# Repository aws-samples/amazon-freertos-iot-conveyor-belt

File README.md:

## IoT Conveyor Belt

A 3D Printed Conveyor belt that runs Amazon FreeRTOS to control conveyor direction and report conveyor telemetry data using Amazon's IoT service.

## License

This library is licensed under the Apache 2.0 License.

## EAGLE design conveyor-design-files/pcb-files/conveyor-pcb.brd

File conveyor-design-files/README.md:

# Assembly Instructions Coming Soon!
We are currently working on detailed assembly instructions and a bill of materials so you can build a conveyor belt your self. [Check out the assembly-instructions branch to see the work in progress](
https://github.com/aws-samples/amazon-freertos-iot-conveyor-belt/tree/assembly-instructions/conveyor-design-files/assembly-instructions)

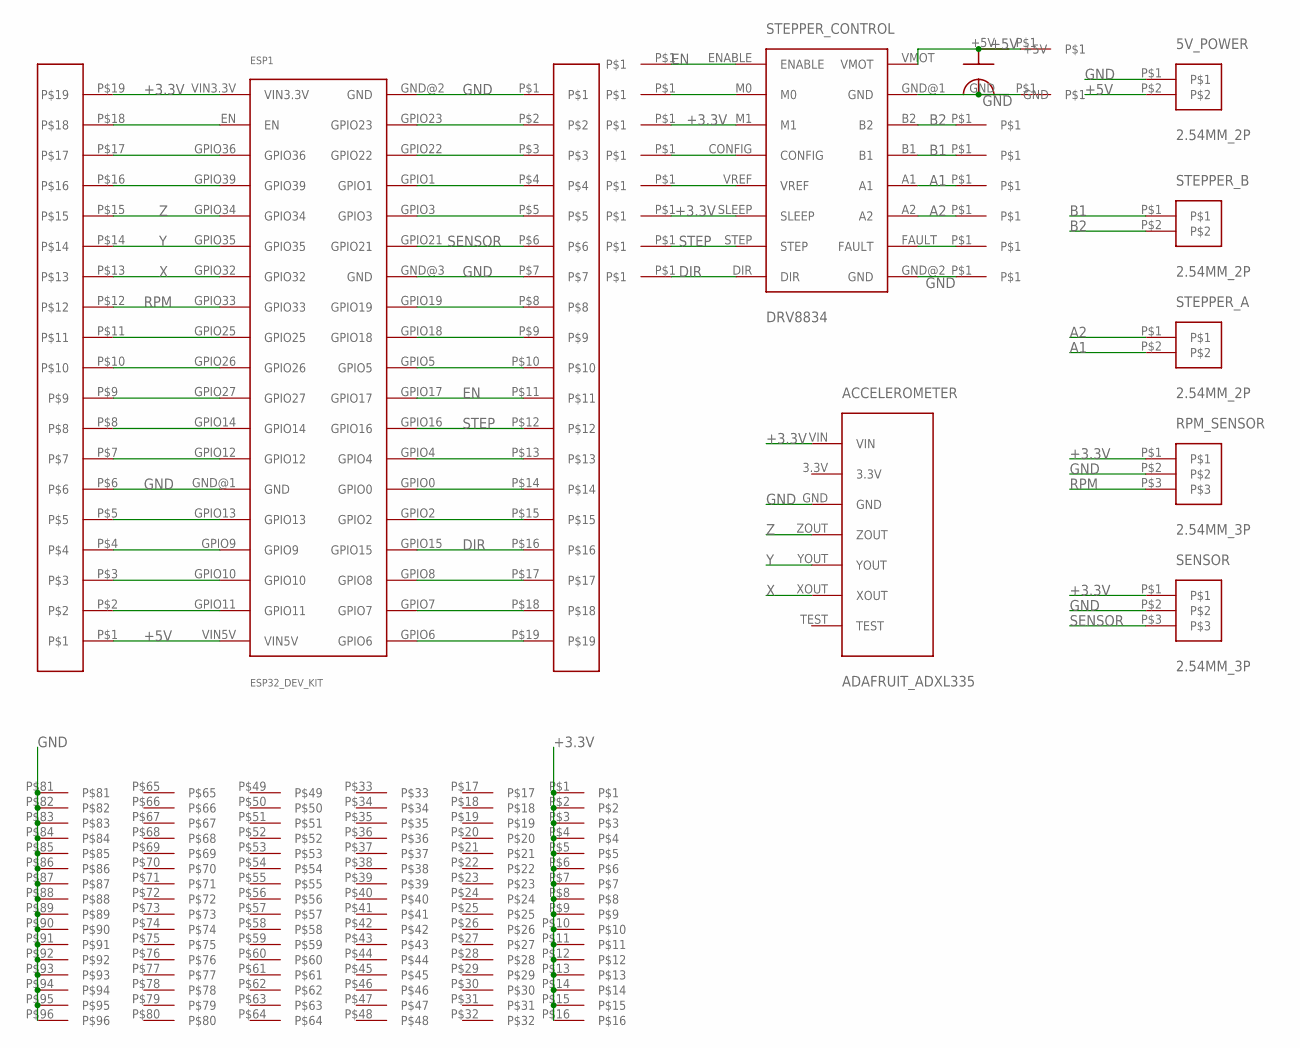
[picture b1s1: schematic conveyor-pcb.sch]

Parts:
5V_POWER: 2.54MM_2P
ACCELEROMETER: ADAFRUIT_ADXL335
ESP1: ESP32_DEV_KIT
RPM_SENSOR: 2.54MM_3P
SENSOR: 2.54MM_3P
STEPPER_A: 2.54MM_2P
STEPPER_B: 2.54MM_2P
STEPPER_CONTROL: DRV8834
U$1, U$2: 19PINHEADER
U$3: PERFBOARD_CONVEYOR
U$4, U$5, U$6, U$7, U$8, U$9, U$10, U$11, U$12, U$13, U$14, U$15, U$16, U$17, U$18, U$19: 1PIN_HEADER
U$20: CAP_100UF

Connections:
+3.3V: ACCELEROMETER.VIN, ESP1.VIN3.3V, RPM_SENSOR.P$1, SENSOR.P$1, STEPPER_CONTROL.M1, STEPPER_CONTROL.SLEEP, U$2.P$19, U$3.P$1, U$3.P$2, U$3.P$3, U$3.P$4, U$3.P$5, U$3.P$6, U$3.P$7, U$3.P$8, U$3.P$9, U$3.P$10, U$3.P$11, U$3.P$12, U$3.P$13, U$3.P$14, U$3.P$15, U$3.P$16, U$6.P$1, U$9.P$1
+5V: 5V_POWER.P$2, ESP1.VIN5V, STEPPER_CONTROL.VMOT, U$2.P$1, U$19.P$1, U$20.+5V
A1: STEPPER_A.P$2, STEPPER_CONTROL.A1, U$15.P$1
A2: STEPPER_A.P$1, STEPPER_CONTROL.A2, U$14.P$1
B1: STEPPER_B.P$1, STEPPER_CONTROL.B1, U$16.P$1
B2: STEPPER_B.P$2, STEPPER_CONTROL.B2, U$17.P$1
DIR: ESP1.GPIO15, STEPPER_CONTROL.DIR, U$1.P$16, U$11.P$1
EN: ESP1.GPIO17, STEPPER_CONTROL.ENABLE, U$1.P$11, U$4.P$1
GND: 5V_POWER.P$1, ACCELEROMETER.GND, ESP1.GND@1 (GND), ESP1.GND@2 (GND), ESP1.GND@3 (GND), RPM_SENSOR.P$2, SENSOR.P$2, STEPPER_CONTROL.GND@1 (GND), STEPPER_CONTROL.GND@2 (GND), U$1.P$1, U$1.P$7, U$2.P$6, U$3.P$81, U$3.P$82, U$3.P$83, U$3.P$84, U$3.P$85, U$3.P$86, U$3.P$87, U$3.P$88, U$3.P$89, U$3.P$90, U$3.P$91, U$3.P$92, U$3.P$93, U$3.P$94, U$3.P$95, U$3.P$96, U$12.P$1, U$18.P$1, U$20.GND
unnamed: STEPPER_CONTROL.M0, U$5.P$1
unnamed: STEPPER_CONTROL.CONFIG, U$7.P$1
unnamed: STEPPER_CONTROL.VREF, U$8.P$1
unnamed: ESP1.GPIO11, U$2.P$2
unnamed: ESP1.GPIO10, U$2.P$3
unnamed: ESP1.GPIO9, U$2.P$4
unnamed: ESP1.GPIO13, U$2.P$5
unnamed: ESP1.GPIO12, U$2.P$7
unnamed: ESP1.GPIO27, U$2.P$9
unnamed: ESP1.GPIO26, U$2.P$10
unnamed: ESP1.GPIO25, U$2.P$11
unnamed: STEPPER_CONTROL.FAULT, U$13.P$1
unnamed: ESP1.EN, U$2.P$18
unnamed: ESP1.GPIO23, U$1.P$2
unnamed: ESP1.GPIO22, U$1.P$3
unnamed: ESP1.GPIO1, U$1.P$4
unnamed: ESP1.GPIO3, U$1.P$5
unnamed: ESP1.GPIO19, U$1.P$8
unnamed: ESP1.GPIO18, U$1.P$9
unnamed: ESP1.GPIO36, U$2.P$17
unnamed: ESP1.GPIO5, U$1.P$10
unnamed: ESP1.GPIO4, U$1.P$13
unnamed: ESP1.GPIO0, U$1.P$14
unnamed: ESP1.GPIO2, U$1.P$15
unnamed: ESP1.GPIO8, U$1.P$17
unnamed: ESP1.GPIO7, U$1.P$18
unnamed: ESP1.GPIO6, U$1.P$19
P$8: ESP1.GPIO14, U$2.P$8
P$16: ESP1.GPIO39, U$2.P$16
RPM: ESP1.GPIO33, RPM_SENSOR.P$3, U$2.P$12
SENSOR: ESP1.GPIO21, SENSOR.P$3, U$1.P$6
STEP: ESP1.GPIO16, STEPPER_CONTROL.STEP, U$1.P$12, U$10.P$1
X: ACCELEROMETER.XOUT, ESP1.GPIO32, U$2.P$13
Y: ACCELEROMETER.YOUT, ESP1.GPIO35, U$2.P$14
Z: ACCELEROMETER.ZOUT, ESP1.GPIO34, U$2.P$15

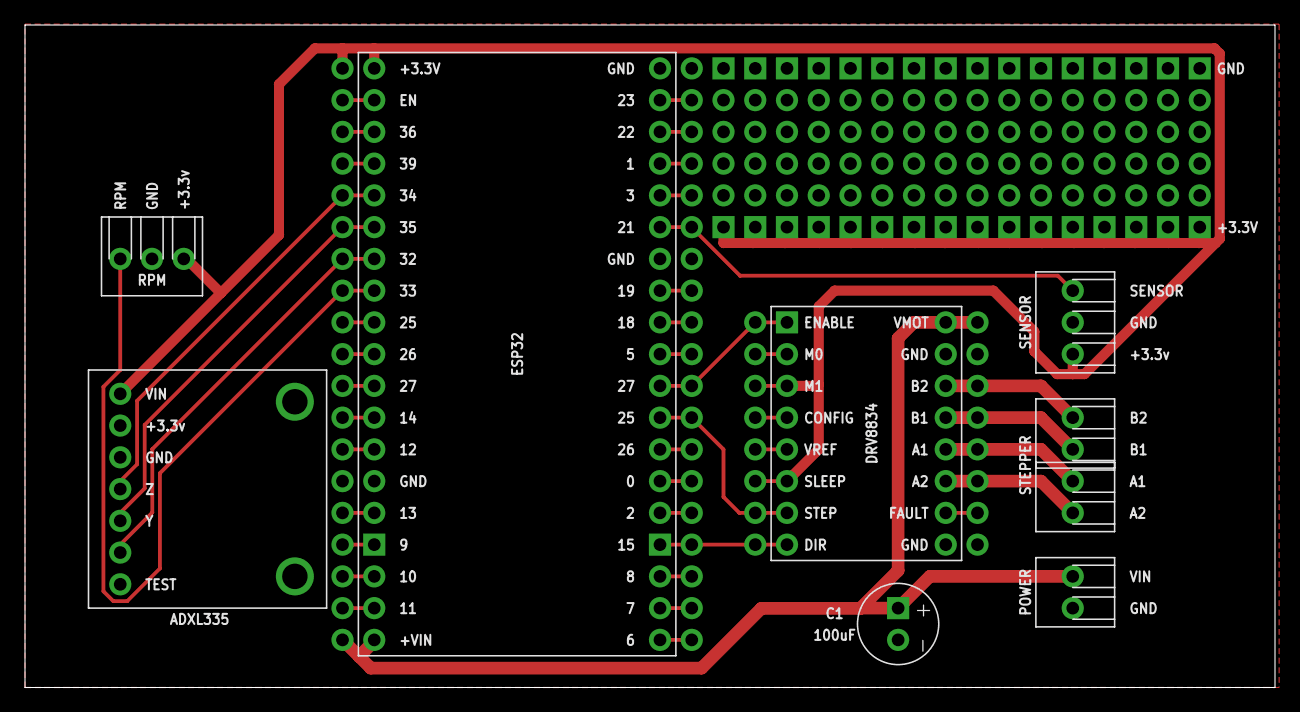
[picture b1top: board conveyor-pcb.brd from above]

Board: 2 copper layers, 100.0 x 53.0 mm, 28 parts (0 on the bottom side), 44 nets.

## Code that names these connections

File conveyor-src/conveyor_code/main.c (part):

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/* Stack size for watchdog task. */
#define WATCHDOG_TASK_STACK_SIZE            ( ( uint16_t ) configMINIMAL_STACK_SIZE * ( uint16_t ) 5 )

/* Input GPIO pin for hall effect sensor */
#define RPM_PIN                             33
#define GPIO_BIT_MASK                       ( 1ULL << GPIO_NUM_33 )

/* Delay for watchdog task. */
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/* Number of times wifi can fail to connect before we restart ESP32. */
#define WIFI_FAIL_LIMIT                     20

/* GPIO pin for the conveyor belt's sensor plugin. */
#define SENSOR_PIN                          21

/* Declare xPixels array. See aws_conveyor_shared.h for more information. */
rgbVal *xPixels;
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void vApplicationDaemonTaskStartupHook( void );

/**
 * @brief Configures GPIO pins, rpm interrupt, and accelerometer
 */
static void prvConfigurePeripherals( void );

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{
    if( SYSTEM_Init() == pdPASS )
    {
        /* Call prvConfigurePeripherals() to set up GPIO pins, rpm interrupt, accelerometer, and LED. */
        prvConfigurePeripherals();

        /* Create the conveyor demo main task */
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    io_conf.pull_up_en = GPIO_PULLUP_ENABLE;
    gpio_config( &io_conf );
    gpio_install_isr_service( 0 );
    gpio_isr_handler_add( RPM_PIN, vRpmInterruptHandler, ( void * ) RPM_PIN );

    /* Configuration for accelerometer */
    adc1_config_width( ADC_WIDTH_BIT_12 );
    adc1_config_channel_atten( ADC1_CHANNEL_4, ADC_ATTEN_DB_11 ); //X -> GPIO32
    adc1_config_channel_atten( ADC1_CHANNEL_7, ADC_ATTEN_DB_11 ); //Y -> GPIO35
    adc1_config_channel_atten( ADC1_CHANNEL_6, ADC_ATTEN_DB_11 ); //Z -> GPIO34

    /* Configure hardware timer, alarm, and interrupt for stepper motor control. */
    vConfigureTimer();

    /* Initialize LED. */
    ws2812_init( SENSOR_PIN );
}

/*-----------------------------------------------------------*/
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
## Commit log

2018-11-09 Creating initial file from template
2018-11-09 Updating initial README.md from template
2018-11-09 Adding conveyor code
2018-11-20 Adding pcb design files
2018-11-20 Adding STL files
2018-11-20 adding gitignore
2018-11-21 updates to pcb files
2018-11-21 minor folder edit
2018-11-21 adding copyright to PCB files
2018-11-28 stub for assembly instructions
2018-11-28 adding Bill of Materials
2018-11-28 Electronics and 3D printing instructions
2018-11-28 images
2018-12-15 breaking instructions into separate steps
2018-12-15 fleshing out the heat set insert section
2018-12-15 fleshing out pulley section
2018-12-15 adding link to assembly-instructions branch
2018-12-19 added version to the amazon-freertos submodules to .gitmodules
2018-12-19 pinning submodule to v1.4.1
2018-12-19 fixing AmazonFreeRTOS submodule to v1.3.1
2018-12-20 adding pulley assembly instructions
2018-12-20 removed heat set insert section from pulley section
2018-12-20 fleshing out electronics section, minor fixes to 3d printing section
2018-12-21 fleshing out final assembly instructions
2018-12-21 adding more instructions to final assembly section
2018-12-21 minor edits
2018-12-22 Shorter legs for smaller printers
    Shortened legs for 3-D printing, that will fit smaller printers (210x210mm printbed size) in stl and OpenSCAD format(http://www.openscad.org/) format.
2019-03-11 Changes for reset logic
2019-09-26 Updating Documentation Links
    The Expressif ESP32 documentation has changed for new versions so the referenced links are no longer valid. Updated the links to reference the ESP32 tool chain version that we are using.
2019-09-26 New version of conveyor belt pulley
    This is a new design for the conveyor belt drive pulley and idler pulley. Instead of using heat set inserts and a set screw to hold the M8 rod in place, the new design uses two M8 lock nuts that are 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
2019-11-12 Update aws_conveyor_telemetry.c
    Modifications made to provide a unique client id and topic for your thing.
2019-11-12 Added clarification to configure.sh prompts
2019-11-12 Updated readme with new suggested topics
2019-11-12 Updated BOM
    Added addition M8 nuts and M2 4mm screws
2019-11-12 Update BOM Links
2019-11-12 Update aws_conveyor_telemetry.c
    Forgot to close comment
2019-11-14 Update aws_conveyor_telemetry.c
    Fixed conflicting clientid

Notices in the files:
conveyor-src/conveyor_code/main.c:
Copyright 2018 Amazon.com, Inc. or its affiliates. All Rights Reserved.
SPDX-License-Identifier: Apache-2.0
SPDX-License-Identifier: MIT
